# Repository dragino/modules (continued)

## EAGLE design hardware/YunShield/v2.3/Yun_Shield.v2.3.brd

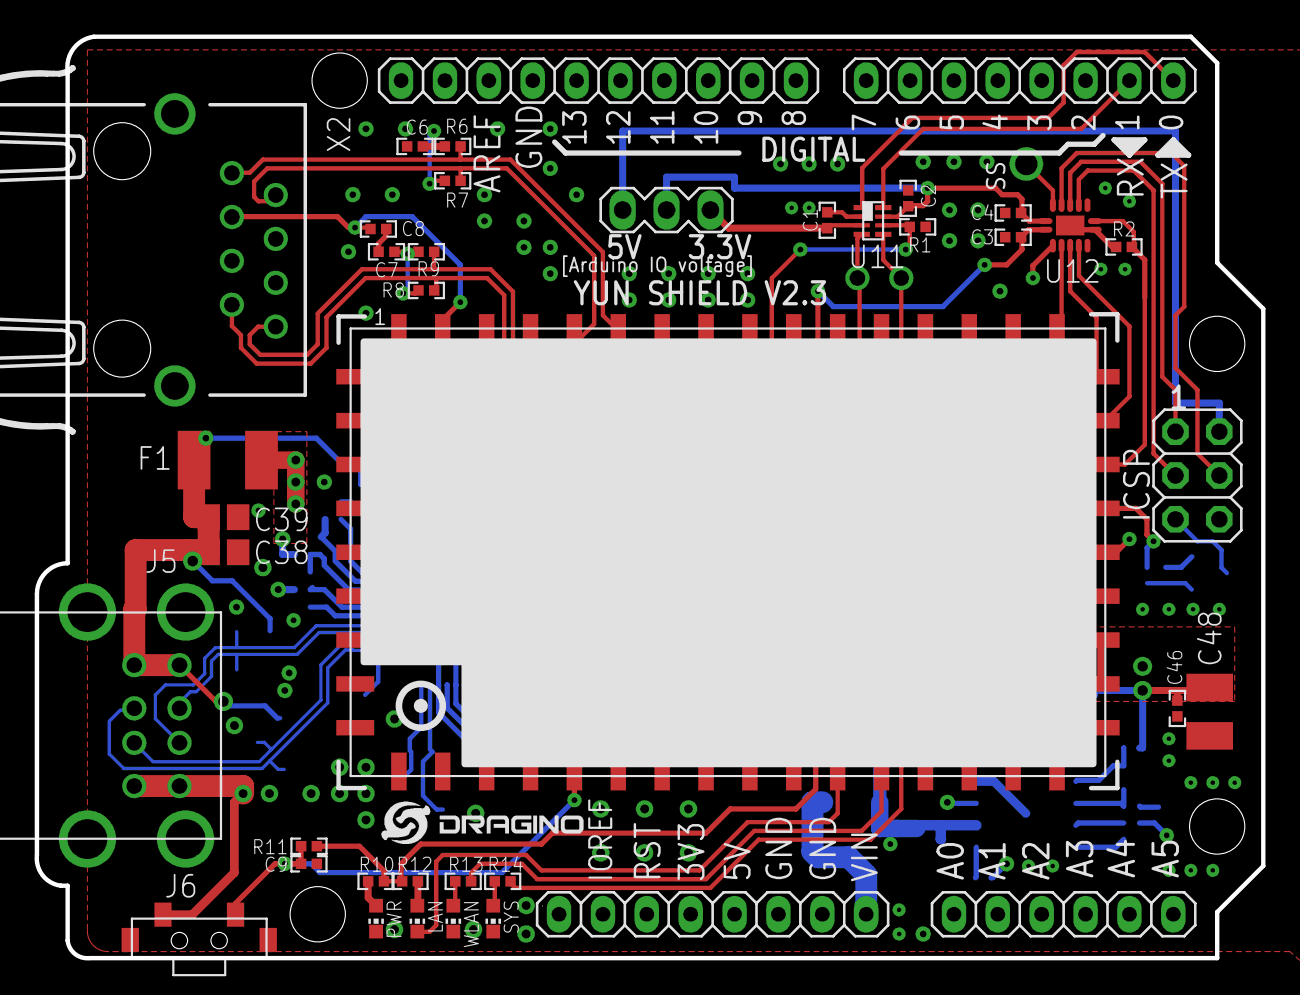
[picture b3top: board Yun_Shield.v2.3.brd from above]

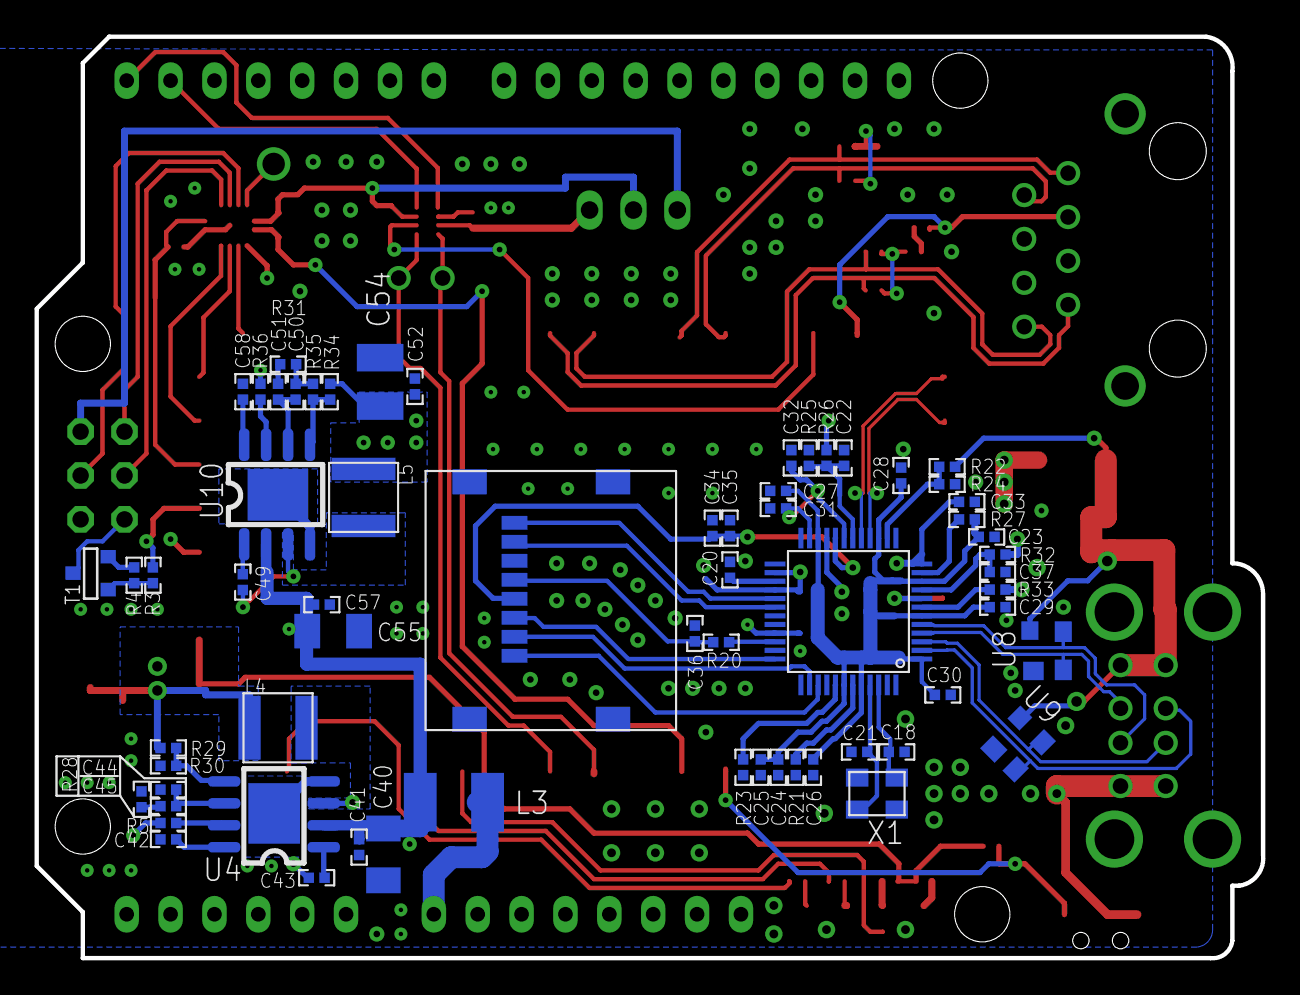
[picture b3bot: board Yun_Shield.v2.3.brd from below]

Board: 4 copper layers, 71.0 x 53.3 mm, 106 parts (64 on the bottom side), 81 nets.

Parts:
C1, C2, C3, C4, C27, C28, C29, C30, C33, C34: 0.1uF; C0402
C6, C7, C8: 0.1u 10v; C0402
C9: 0.1u NL; C0402
C18, C21: 18pF; C0402
C20, C22, C25, C35: 1uF; C0402
C23, C24, C26, C31, C32: 4.7uF; C0402
C36: 10pf,NL; C0402
C37: 2.2uF; C0402
C38, C39: 10uF; C0805
C40: 10u,25v; C1206K
C41, C44, C46, C50, C52, C57: NL; C0402
C42, C58: 0.1u,10v; C0402
C43, C49: 0.01u,16v; C0402
C45, C51: 3900pf,25v; C0402
C48, C54: 22u,10v; C1210
C55: 10uf,25v; C1206K
F1: Fuse , 1A; L1812
ICSP: ICSP; 2X03
J2, J3: 8x1F-H8.5; 1X08
J4: 6x1F-H8.5; 1X06
J5: USB-CON-A-DUAL; USB-DUAL-JS-AF10-002
J6: SWITCHTS-017; TS-017
JP1: 10x1F-H8.5; 1X10
L3: 1A; L1812
L4: 10uH /SWPA4020S100MT; SWPA4020S
L5: 15uH / SWPA4030S150MT; SWPA4020S
LAN: Yellow; CHIP-LED0603
PWR: Yellow-Green; CHIP-LED0603
R1, R2, R3, R4: 10k; R0402
R5, R36: 100K; R0402
R6, R7, R8, R9: 49.9R; R0402
R10, R12: 330R; R0402
R11, R24, R30, R35: 10K; R0402
R13, R14: 270R; R0402
R20, R27, R32, R33: 0R; R0402
R21: 680; R0402
R22: 5.1K; R0402
R23: 330; R0402
R25: 470K; R0402
R26: 47K; R0402
R28, R31: 6.81K; R0402
R29: 26.1K; R0402
R34: 45.3K; R0402
SV1: MA03-1
SYS: WHITE; CHIP-LED0603
T1: BSS138/SOT23; SOT-23
TP1: TEST-POINTTH; TEST-POINT-TH
U1: HE; HE50
U3: AU6353; AU6350_LQFP-48
U4, U10: RT8250; RT8250-SOP8
U8, U9: YSSR05; SOT143
U11: NTB0102GT; NXP-SOT833-1
U12: NTB0104; DHVQFN14
U$1: LOGO-NEW; LOGO-SILK-NEW
U$14: RIONET_472192001_SD
WLAN: BLUE; CHIP-LED0603
X1: 12Mhz; SMARTPRJ_CRYSTAL-3.2-2.5
X2: RJ111BE

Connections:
2.5V: C3.2, U1.36, U12.1
+3V3: C1.2, C46.2, C48.1, L4.P$2, R10.1, R11.2, R12.1, R29.2, SV1.3, U1.23, U1.24, U11.3
+5V: ICSP.2, J3.5, SV1.1
+5V_USB: C52.2, C54.1, F1.2, L5.P$2, R26.2, R32.1, R34.2
/RESET: ICSP.5, T1.1
CHIP_RESETN: C22.1, R25.1, R26.1, U3.18
CPWR_V33: C34.1, C35.1, U3.20, U$14.4
CTRL_2.0V: C8.1, U1.2, X2.3
DP1_OVRCUR: R22.1, R24.2, U3.14
GND: C1.1, C2.1, C3.1, C4.1, C6.2, C7.2, C8.2, C9.2, C18.2, C20.2, C21.2, C22.2, C23.2, C24.2, C25.2, C26.2, C27.2, C28.2, C29.2, C30.2, C31.2, C32.2, C33.2, C34.2, C35.2, C36.2, C37.2, C38.1, C39.1, C40.2, C41.2, C42.2, C44.1, C46.1, C48.2, C50.1, C52.1, C54.2, C55.2, C57.2, C58.2, ICSP.6, J3.6, J3.7, J5.4, J5.8, J6.P$2, JP1.7, PWR.C, R1.1, R2.1, R4.2, R21.1, R23.2, R24.1, R25.2, R28.1, R30.1, R31.1, R35.1, SYS.C, T1.2, U1.1, U1.4, U1.7, U1.10, U1.13, U1.22, U1.25, U1.26, U1.32, U1.35, U1.40, U1.42, U1.44, U1.45, U1.48, U3.8, U3.21, U3.25, U3.26, U3.28, U3.33, U4.4, U4.9, U8.1, U9.1, U10.4, U10.9, U11.2, U12.7, U12.EXP, U$14.6, U$14.G1, U$14.G2, U$14.G3, U$14.G4, WLAN.C, X1.2, X1.4
GPIO18: U1.18, U12.5
GPIO19: R2.2, U1.19, U12.8
GPIO20: R3.2, U1.20
GPIO21: U1.16, U12.3
GPIO22: U1.17, U12.4
GPIO23: U1.21, U12.2
GPIO24: R1.2, U1.3, U11.6
GPIO28: R14.1, U1.27
JUMPSTART: C9.1, J6.P$1, R11.1, U1.37
LED_P0: LAN.C, U1.31
LED_WLAN: R13.1, U1.30
MISO: ICSP.1, U12.11
MOSI: ICSP.4, U12.12
unnamed: R3.1, R4.1, T1.3
unnamed: C6.1, R6.1, R7.1
unnamed: PWR.A, R10.2
unnamed: C7.1, R8.1, R9.1
unnamed: LAN.A, R12.2
unnamed: R13.2, WLAN.A
unnamed: R14.2, SYS.A
unnamed: R5.1, U4.7
unnamed: R23.1, U3.41
unnamed: R21.2, U3.43
unnamed: C42.1, U4.8
unnamed: C36.1, R20.2, U$14.5
unnamed: C20.1, U3.27
unnamed: R27.2, U3.11
unnamed: C43.1, U4.1
unnamed: C43.2, L4.P$1, U4.3
unnamed: C44.2, C45.2, U4.6
unnamed: C45.1, R28.2
unnamed: C37.1, R32.2, U3.9
unnamed: R33.2, U3.7
unnamed: R29.1, R30.2, U4.5
unnamed: C49.1, U10.1
unnamed: C49.2, L5.P$1, U10.3
unnamed: C50.2, C51.2, U10.6
unnamed: C51.1, R31.2
unnamed: R34.1, R35.2, U10.5
unnamed: R36.1, U10.7
unnamed: C58.1, U10.8
unnamed: C40.1, C41.1, C55.1, C57.1, L3.2, R5.2, R36.2, U4.2, U10.2
P0_RX_N: R9.2, U1.8, X2.8
P0_RX_P: R8.2, U1.9, X2.7
P0_TX_N: R7.2, U1.5, X2.2
P0_TX_P: R6.2, U1.6, X2.1
P1_P2_PWR: C38.2, C39.2, F1.1, J5.1, J5.5, R22.2, U8.4, U9.4
RX: J2.1, U11.1
SCK: ICSP.3, U12.10
SD_CLK: R20.1, U3.34
SD_CMD: U3.36, U$14.3
SD_DAT0: U3.30, U$14.7
SD_DAT1: U3.29, U$14.8
SD_DAT2: U3.39, U$14.1
SD_DAT3: U3.38, U$14.2
SS: TP1.P$1, U12.13
TX: J2.2, U11.8
UART_RX: U1.33, U11.5
UART_TX: U1.34, U11.4
USB3_D_N: J5.6, U3.2, U9.2
USB3_D_P: J5.7, U3.3, U9.3
USB4_D_N: J5.2, U3.4, U8.2
USB4_D_P: J5.3, U3.5, U8.3
USB_N: U1.50, U3.17
USB_P: U1.49, U3.16
VCC1.8: C31.1, C32.1, C33.1, R33.1, U3.12, U3.19, U3.23
VCC3.3: C23.1, C24.1, C25.1, C26.1, C27.1, C28.1, C29.1, C30.1, R27.1, U3.1, U3.6, U3.10, U3.15, U3.22, U3.42, U3.44
VDC: C2.2, C4.2, SV1.2, U11.7, U12.14
VIN: J3.8, L3.1
XSCI: C18.1, U3.46, X1.1
XSCO: C21.1, U3.45, X1.3

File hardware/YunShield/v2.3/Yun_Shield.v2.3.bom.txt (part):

Partlist exported from D:/Projects/Dragino/Dragon Board V1.0/Yun Shield/v2.3/Yun_Shield.v2.3.sch at 2015/9/6 16:31

Part Value                 Device                   Package                  Description                             MF MPN OC_FARNELL OC_NEWARK
C1   0.1uF                 C-EUC0402                C0402                    CAPACITOR, European symbol                                         
C2   0.1uF                 C-EUC0402                C0402                    CAPACITOR, European symbol                                         
C3   0.1uF                 C-EUC0402                C0402                    CAPACITOR, European symbol                                         
C4   0.1uF                 C-EUC0402                C0402                    CAPACITOR, European symbol                                         
C6   0.1u 10v              C-EUC0402                C0402                    CAPACITOR, European symbol                                         
C7   0.1u 10v              C-EUC0402                C0402                    CAPACITOR, European symbol                                         
C8   0.1u 10v              C-EUC0402                C0402                    CAPACITOR, European symbol                                         
C9   0.1u NL               C-EUC0402                C0402                    CAPACITOR, European symbol                                         
C18  18pF                  C-EUC0402                C0402                    CAPACITOR, European symbol                                         
C20  1uF                   C-EUC0402                C0402                    CAPACITOR, European symbol                                         
C21  18pF                  C-EUC0402                C0402                    CAPACITOR, European symbol                                         
C22  1uF                   C-EUC0402                C0402                    CAPACITOR, European symbol                                         
C23  4.7uF                 C-EUC0402                C0402                    CAPACITOR, European symbol                                         
C24  4.7uF                 C-EUC0402                C0402                    CAPACITOR, European symbol                                         
C25  1uF                   C-EUC0402                C0402                    CAPACITOR, European symbol                                         
C26  4.7uF                 C-EUC0402                C0402                    CAPACITOR, European symbol                                         
C27  0.1uF                 C-EUC0402                C0402                    CAPACITOR, European symbol                                         
C28  0.1uF                 C-EUC0402                C0402                    CAPACITOR, European symbol                                         
C29  0.1uF                 C-EUC0402                C0402                    CAPACITOR, European symbol                                         
C30  0.1uF                 C-EUC0402                C0402                    CAPACITOR, European symbol                                         
C31  4.7uF                 C-EUC0402                C0402                    CAPACITOR, European symbol                                         
C32  4.7uF                 C-EUC0402                C0402                    CAPACITOR, European symbol                                         
C33  0.1uF                 C-EUC0402                C0402                    CAPACITOR, European symbol                                         
C34  0.1uF                 C-EUC0402                C0402                    CAPACITOR, European symbol                                         
C35  1uF                   C-EUC0402                C0402                    CAPACITOR, European symbol                                         
C36  10pf,NL               C-EUC0402                C0402                    CAPACITOR, European symbol                                         
C37  2.2uF                 C-EUC0402                C0402                    CAPACITOR, European symbol                                         
C38  10uF                  C-EUC0805                C0805                    CAPACITOR, European symbol                                         
C39  10uF                  C-EUC0805                C0805                    CAPACITOR, European symbol                                         
C40  10u,25v               C-EUC1206K               C1206K                   CAPACITOR, European symbol                                         
C41  NL                    C-EUC0402                C0402                    CAPACITOR, European symbol                                         
C42  0.1u,10v              C-EUC0402                C0402                    CAPACITOR, European symbol                                         
C43  0.01u,16v             C-EUC0402                C0402                    CAPACITOR, European symbol                                         
C44  NL                    C-EUC0402                C0402                    CAPACITOR, European symbol                                         
C45  3900pf,25v            C-EUC0402                C0402                    CAPACITOR, European symbol                                         
C46  NL                    C-EUC0402                C0402                    CAPACITOR, European symbol                                         
C48  22u,10v               C-EUC1210                C1210                    CAPACITOR, European symbol                                         
C49  0.01u,16v             C-EUC0402                C0402                    CAPACITOR, European symbol                                         
C50  NL                    C-EUC0402                C0402                    CAPACITOR, European symbol                                         
C51  3900pf,25v            C-EUC0402                C0402                    CAPACITOR, European symbol                                         
C52  NL                    C-EUC0402                C0402                    CAPACITOR, European symbol                                         
C54  22u,10v               C-EUC1210                C1210                    CAPACITOR, European symbol                                         
C55  10uf,25v              C-EUC1206K               C1206K                   CAPACITOR, European symbol                                         
C57  NL                    C-EUC0402                C0402                    CAPACITOR, European symbol                                         
C58  0.1u,10v              C-EUC0402                C0402                    CAPACITOR, European symbol                                         
F1   Fuse , 1A             FUSE1812                 L1812                    FUSE                                                               
ICSP ICSP                  PINHD-2X3                2X03                     PIN HEADER                                                         
J2   8x1F-H8.5             PINHD-1X8                1X08                     PIN HEADER                                                         
J3   8x1F-H8.5             PINHD-1X8                1X08                     PIN HEADER                                                         
J4   6x1F-H8.5             PINHD-1X6                1X06                     PIN HEADER                                                         
J5   USB-CON-A-DUAL        USB-CON-A-DUAL           USB-DUAL-JS-AF10-002                                                                        
J6   SWITCHTS-017          SWITCHTS-017             TS-017                                                                                      
JP1  10x1F-H8.5            PINHD-1X10               1X10                     PIN HEADER                                                         
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
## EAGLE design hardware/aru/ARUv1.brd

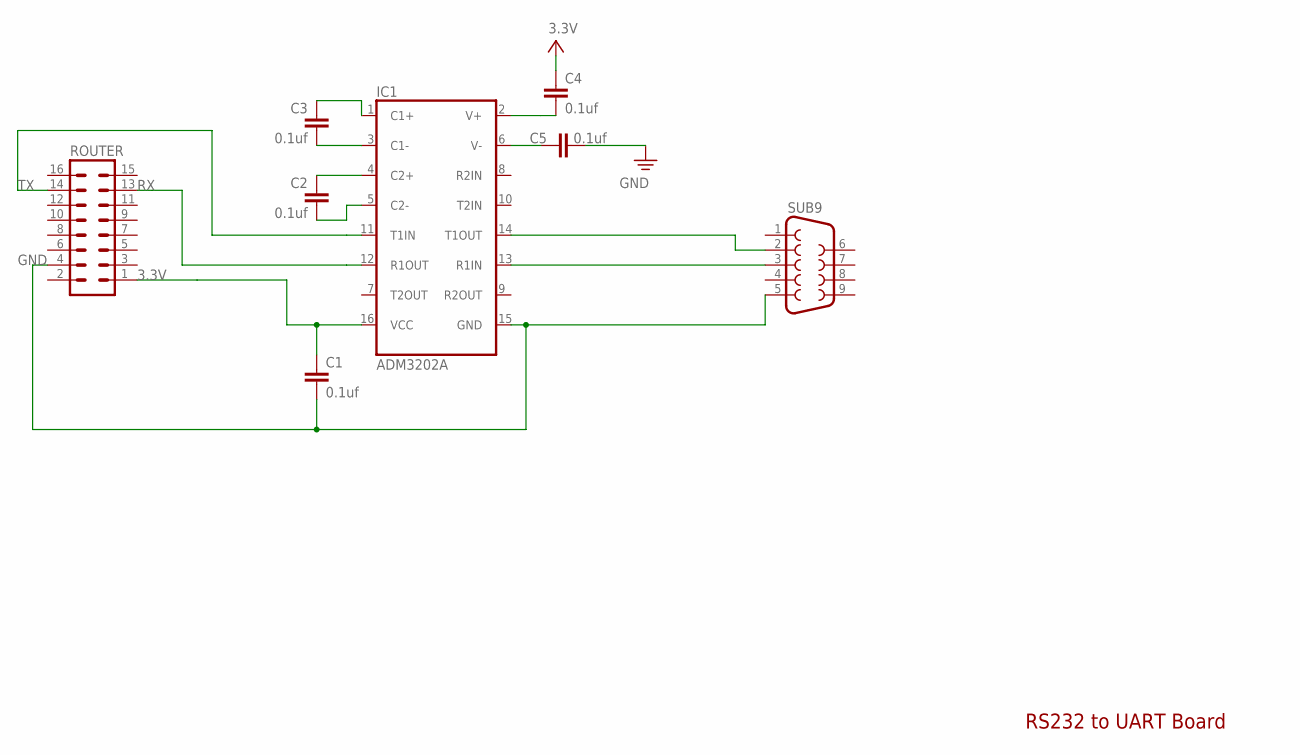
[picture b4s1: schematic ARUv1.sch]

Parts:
C1, C2, C3, C4, C5: 0.1uf; C0402
IC1: ADM3202A; TSSOP16
ROUTER: MA08-2
SUB9: F09HP

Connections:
3.3V: C1.1, C4.1, IC1.16 (VCC), ROUTER.1
GND: C1.2, C5.1, IC1.15 (GND), ROUTER.4, SUB9.5
unnamed: C2.1, IC1.5 (C2-)
unnamed: C2.2, IC1.4 (C2+)
unnamed: C3.2, IC1.3 (C1-)
unnamed: C3.1, IC1.1 (C1+)
unnamed: C4.2, IC1.2 (V+)
unnamed: C5.2, IC1.6 (V-)
unnamed: IC1.14 (T1OUT), SUB9.2
unnamed: IC1.13 (R1IN), SUB9.3
RX: IC1.12 (R1OUT), ROUTER.13
TX: IC1.11 (T1IN), ROUTER.14

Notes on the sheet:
RS232 to UART Board

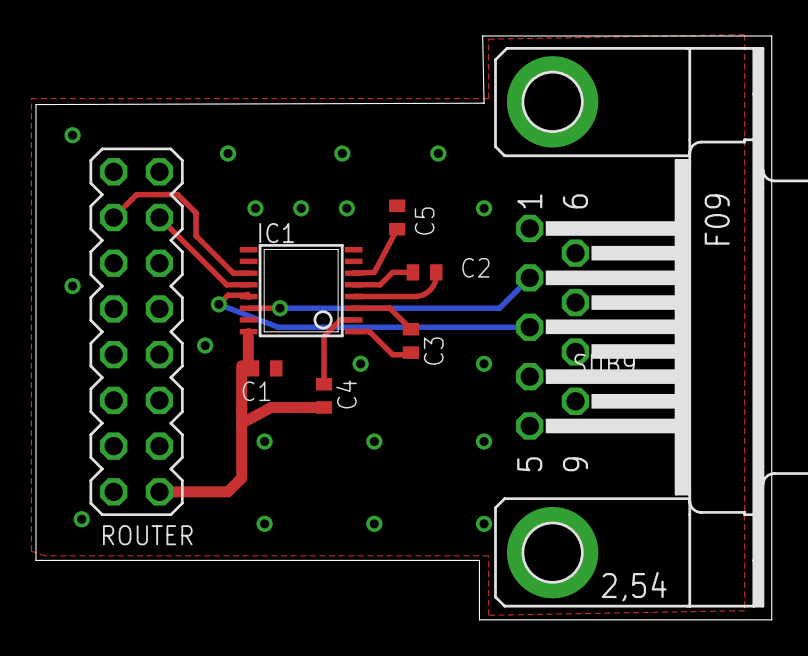
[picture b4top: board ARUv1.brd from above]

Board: 2 copper layers, 40.9 x 32.4 mm, 9 parts (0 on the bottom side), 12 nets.

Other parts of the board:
U$1: LOGO-SILK-15MM

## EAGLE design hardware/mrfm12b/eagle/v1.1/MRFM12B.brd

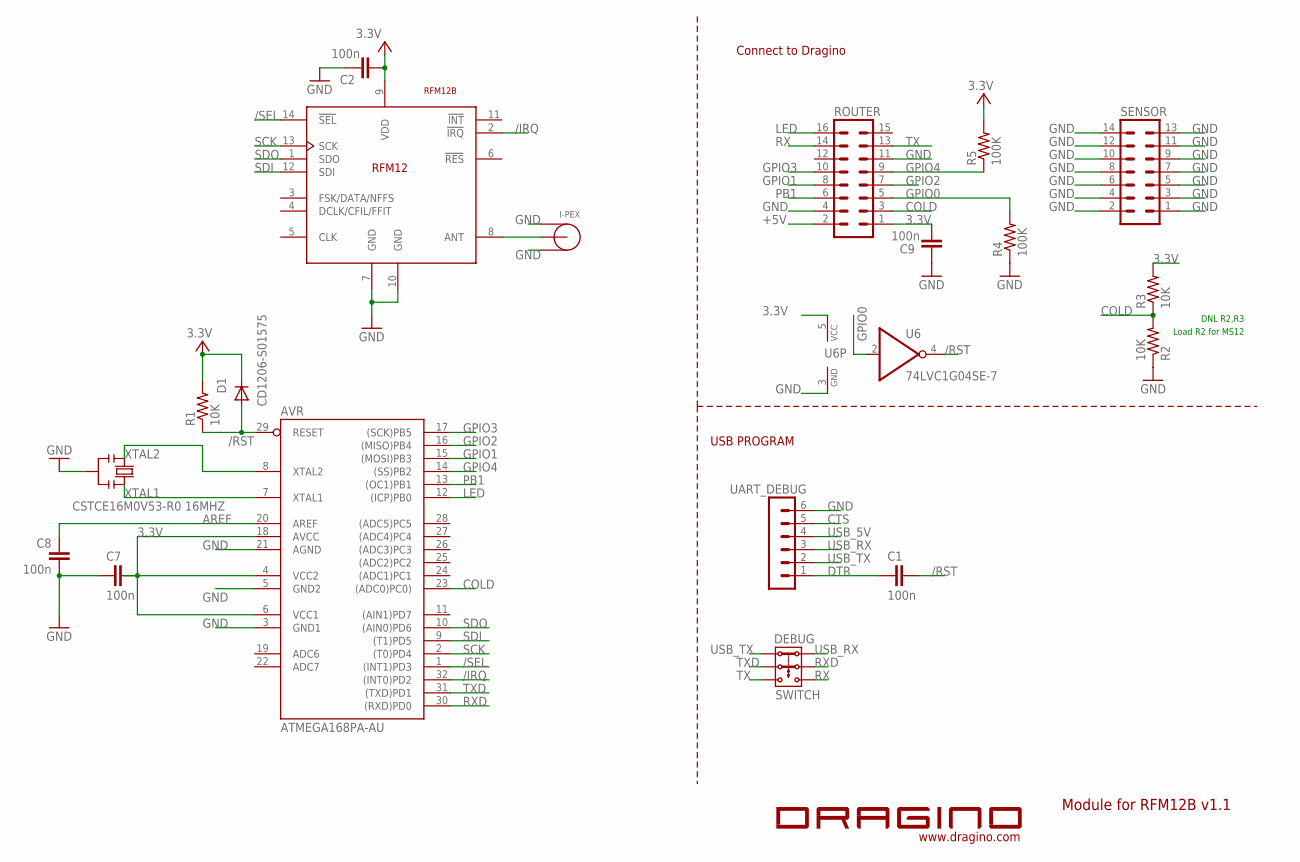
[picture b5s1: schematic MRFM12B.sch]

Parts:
AVR: ATMEGA168PA-AU; SMARTPRJ_TQFP32-08
C1, C2, C7, C8, C9: 100n; C0402
D1: CD1206-S01575; MINIMELF
DEBUG: SWITCH; 2P2T
I-PEX: I-PEX
R1, R2, R3: 10K; R0402
R4, R5: 100K; R0402
RFM12B: RFM12B; RFM12
ROUTER: MA08-2
SENSOR: MA07-2
U6: 74LVC1G04SE-7; SC70-5
U$1: LOGO-SILK; LOGO-SILK-15MM
UART_DEBUG: MA06-1
Y1: CSTCE16M0V53-R0 16MHZ; RESONATOR

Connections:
3.3V: AVR.4 (VCC2), AVR.6 (VCC1), AVR.18 (AVCC), C2.1, C7.1, C9.2, D1.C, R1.2, R3.2, R5.2, RFM12B.9 (VDD), ROUTER.1, U6.5 (VCC)
+5V: ROUTER.2
/IRQ: AVR.32 ((INT0)PD2), RFM12B.2 (!IRQ)
/RST: AVR.29 (RESET), C1.1, D1.A, R1.1, U6.4 (O)
/SEL: AVR.1 ((INT1)PD3), RFM12B.14 (!SEL)
AREF: AVR.20 (AREF), C8.1
COLD: AVR.23 ((ADC0)PC0)), R2.2, R3.1, ROUTER.3
CTS: UART_DEBUG.5
DTR: C1.2, UART_DEBUG.1
GND: AVR.3 (GND1), AVR.5 (GND2), AVR.21 (AGND), C2.2, C7.2, C8.2, C9.1, I-PEX.GND, I-PEX.GND1, R2.1, R4.1, RFM12B.7 (GND), RFM12B.10 (GND), ROUTER.4, ROUTER.11, SENSOR.1, SENSOR.2, SENSOR.3, SENSOR.4, SENSOR.5, SENSOR.6, SENSOR.7, SENSOR.8, SENSOR.9, SENSOR.10, SENSOR.11, SENSOR.12, SENSOR.13, SENSOR.14, U6.3 (GND), UART_DEBUG.6, Y1.2
GPIO0: R4.2, ROUTER.5, U6.2 (I)
GPIO1: AVR.15 ((MOSI)PB3), ROUTER.8
GPIO2: AVR.16 ((MISO)PB4), ROUTER.7
GPIO3: AVR.17 ((SCK)PB5), ROUTER.10
GPIO4: AVR.14 ((SS)PB2), R5.1, ROUTER.9
LED: AVR.12 ((ICP)PB0), ROUTER.16
unnamed: I-PEX.SIG, RFM12B.8 (ANT)
PB1: AVR.13 ((OC1)PB1), ROUTER.6
RX: DEBUG.3.1, ROUTER.14
RXD: AVR.30 ((RXD)PD0), DEBUG.2.1
SCK: AVR.2 ((T0)PD4), RFM12B.13 (SCK)
SDI: AVR.9 ((T1)PD5), RFM12B.12 (SDI)
SDO: AVR.10 ((AIN0)PD6), RFM12B.1 (SDO)
TX: DEBUG.3.2, ROUTER.13
TXD: AVR.31 ((TXD)PD1), DEBUG.2.2
USB_5V: UART_DEBUG.4
USB_RX: DEBUG.1.1, UART_DEBUG.3
USB_TX: DEBUG.1.2, UART_DEBUG.2
XTAL1: AVR.7 (XTAL1), Y1.3
XTAL2: AVR.8 (XTAL2), Y1.1

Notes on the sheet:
Connect to Dragino
Module for RFM12B v1.1
USB PROGRAM
DNL R2,R3
Load R2 for MS12

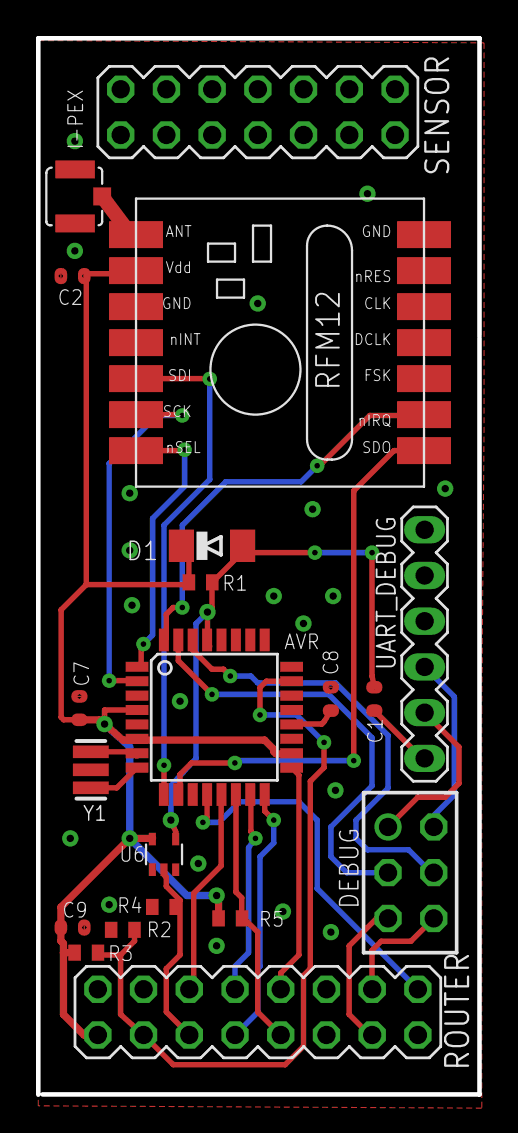
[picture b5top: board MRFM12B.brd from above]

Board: 2 copper layers, 24.5 x 58.7 mm, 21 parts (0 on the bottom side), 27 nets.

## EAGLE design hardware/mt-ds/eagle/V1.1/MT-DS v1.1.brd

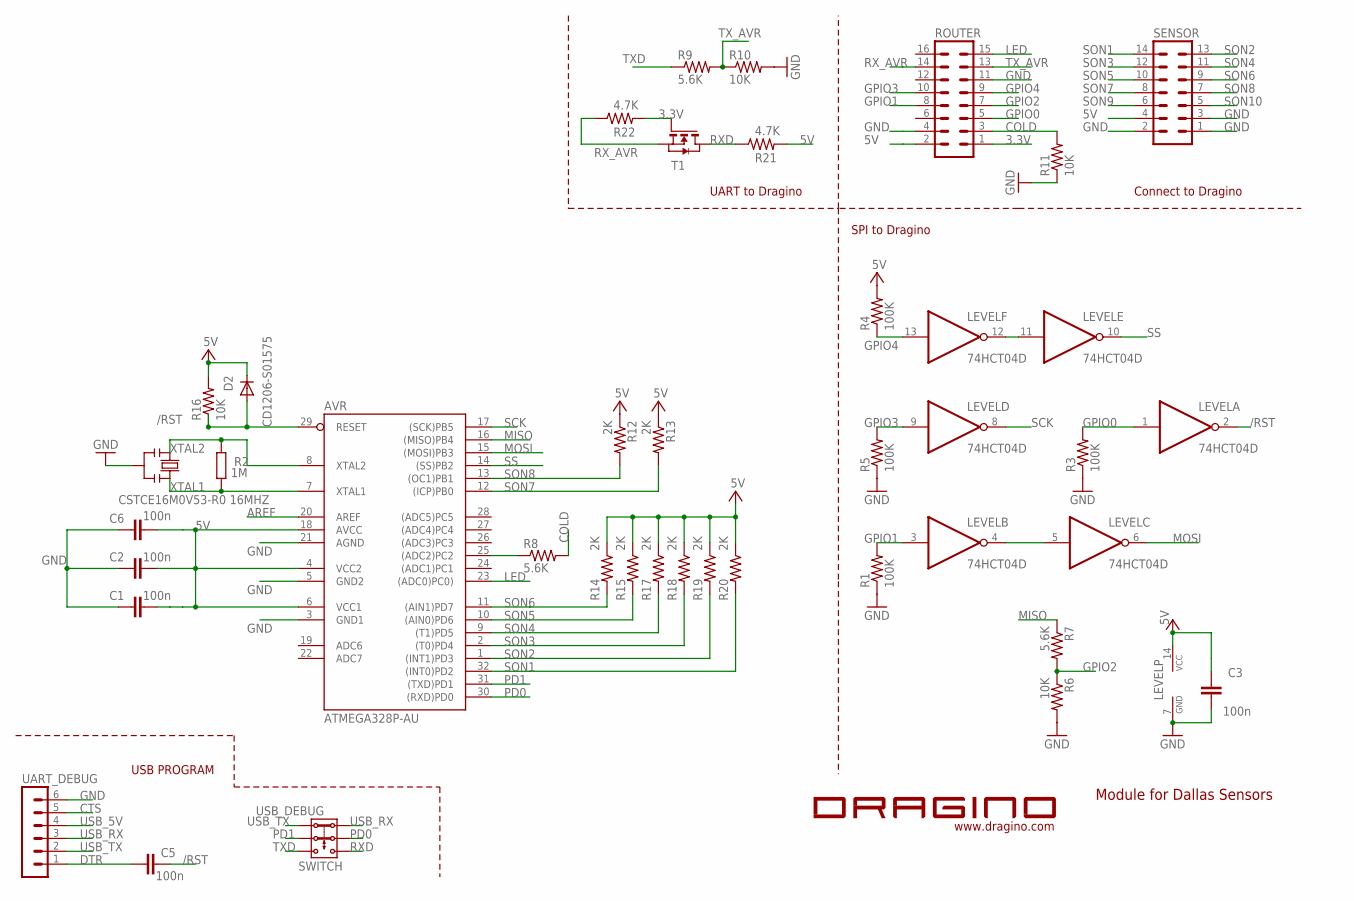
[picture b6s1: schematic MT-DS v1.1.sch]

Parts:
AVR: ATMEGA328P-AU; SMARTPRJ_TQFP32-08
C1, C2, C3, C5, C6: 100n; C0402
D2: CD1206-S01575; MINIMELF
LEVEL: 74HCT04D; SO14
R1, R3, R4, R5: 100K; R0402
R2: 1M; R0402
R6, R10, R11, R16: 10K; R0402
R7, R8, R9: 5.6K; R0402
R12, R13, R14, R15, R17, R18, R19, R20: 2K; R0805
R21, R22: 4.7K; R0805
ROUTER: MA08-2
SENSOR: MA07-2
T1: NMOSFET-SOT23; SOT-23
U$1: LOGO-SILK; LOGO-SILK-15MM
UART_DEBUG: MA06-1
USB_DEBUG: SWITCH; 2P2T
Y2: CSTCE16M0V53-R0 16MHZ; RESONATOR

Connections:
3.3V: R22.2, ROUTER.1, T1.3 (G)
5V: AVR.4 (VCC2), AVR.6 (VCC1), AVR.18 (AVCC), C1.1, C2.1, C3.2, C6.1, D2.C, LEVEL.14 (VCC), R4.2, R12.1, R13.1, R14.1, R15.1, R16.2, R17.1, R18.1, R19.1, R20.1, R21.2, ROUTER.2, SENSOR.4
/RST: AVR.29 (RESET), C5.2, D2.A, LEVEL.2 (O), R16.1
AREF: AVR.20 (AREF)
COLD: R8.2, R11.2, ROUTER.3
CTS: UART_DEBUG.5
DTR: C5.1, UART_DEBUG.1
GND: AVR.3 (GND1), AVR.5 (GND2), AVR.21 (AGND), C1.2, C2.2, C3.1, C6.2, LEVEL.7 (GND), R1.1, R3.1, R5.1, R6.2, R10.2, R11.1, ROUTER.4, ROUTER.11, SENSOR.1, SENSOR.2, SENSOR.3, UART_DEBUG.6, Y2.2
GPIO0: LEVEL.1 (I), R3.2, ROUTER.5
GPIO1: LEVEL.3 (I), R1.2, ROUTER.8
GPIO2: R6.1, R7.2, ROUTER.7
GPIO3: LEVEL.9 (I), R5.2, ROUTER.10
GPIO4: LEVEL.13 (I), R4.1, ROUTER.9
LED: AVR.23 ((ADC0)PC0)), ROUTER.15
MISO: AVR.16 ((MISO)PB4), R7.1
MOSI: AVR.15 ((MOSI)PB3), LEVEL.6 (O)
unnamed: AVR.25 ((ADC2)PC2), R8.1
unnamed: LEVEL.11 (I), LEVEL.12 (O)
unnamed: LEVEL.4 (O), LEVEL.5 (I)
PD0: AVR.30 ((RXD)PD0), USB_DEBUG.2.1
PD1: AVR.31 ((TXD)PD1), USB_DEBUG.2.2
RXD: R21.1, T1.1 (D), USB_DEBUG.3.1
RX_AVR: R22.1, ROUTER.14, T1.2 (S)
SCK: AVR.17 ((SCK)PB5), LEVEL.8 (O)
SON1: AVR.32 ((INT0)PD2), R20.2, SENSOR.14
SON2: AVR.1 ((INT1)PD3), R19.2, SENSOR.13
SON3: AVR.2 ((T0)PD4), R18.2, SENSOR.12
SON4: AVR.9 ((T1)PD5), R17.2, SENSOR.11
SON5: AVR.10 ((AIN0)PD6), R15.2, SENSOR.10
SON6: AVR.11 ((AIN1)PD7), R14.2, SENSOR.9
SON7: AVR.12 ((ICP)PB0), R13.2, SENSOR.8
SON8: AVR.13 ((OC1)PB1), R12.2, SENSOR.7
SON9: SENSOR.6
SON10: SENSOR.5
SS: AVR.14 ((SS)PB2), LEVEL.10 (O)
TXD: R9.1, USB_DEBUG.3.2
TX_AVR: R9.2, R10.1, ROUTER.13
USB_5V: UART_DEBUG.4
USB_RX: UART_DEBUG.3, USB_DEBUG.1.1
USB_TX: UART_DEBUG.2, USB_DEBUG.1.2
XTAL1: AVR.7 (XTAL1), R2.1, Y2.3
XTAL2: AVR.8 (XTAL2), R2.2, Y2.1

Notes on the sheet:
Connect to Dragino
SPI to Dragino
UART to Dragino
USB PROGRAM
Module for Dallas Sensors

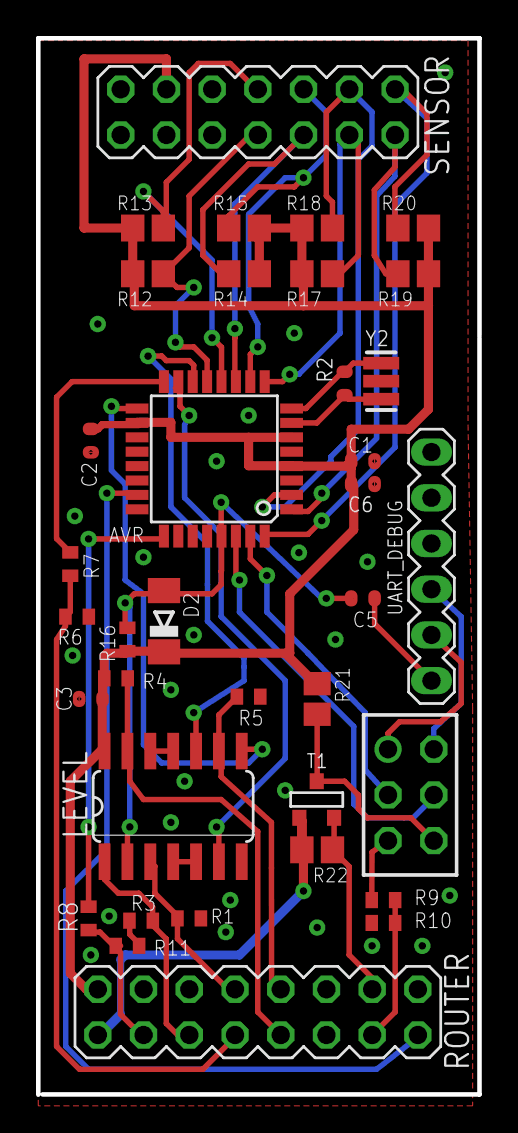
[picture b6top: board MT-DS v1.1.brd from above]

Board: 2 copper layers, 24.5 x 58.7 mm, 37 parts (0 on the bottom side), 37 nets.
